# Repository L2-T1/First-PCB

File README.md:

# First-PCB
This my first PCB for learning and for the Solder activity ran by Hack Club

# Description
This project is creating a circuit board that powers 2 LED's that light up and have their brightness changed by a potentiometer.

# Bill of materials
- 2x LED's
- 2x Resisters
- 1x Single Battery-Cell
- 1x Rotary Potentiometer

# Screenshots

Made by Elliot on Slack 

Made as part of Hack Club Solder

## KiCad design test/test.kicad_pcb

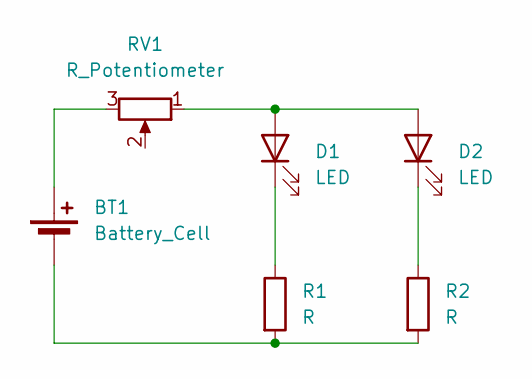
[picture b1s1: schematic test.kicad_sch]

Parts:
BT1: Battery_Cell; BatteryHolder_Keystone_3034_1x20mm
D1, D2: LED; LED_D5.0mm
R1, R2: R; R_Axial_DIN0207_L6.3mm_D2.5mm_P7.62mm_Horizontal
RV1: R_Potentiometer; Potentiometer_Vishay_T73YP_Vertical

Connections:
unnamed: BT1.1 (+), RV1.3
unnamed: BT1.2 (-), R1.2, R2.2
unnamed: D1.2 (A), D2.2 (A), RV1.1
unnamed: D1.1 (K), R1.1
unnamed: D2.1 (K), R2.1

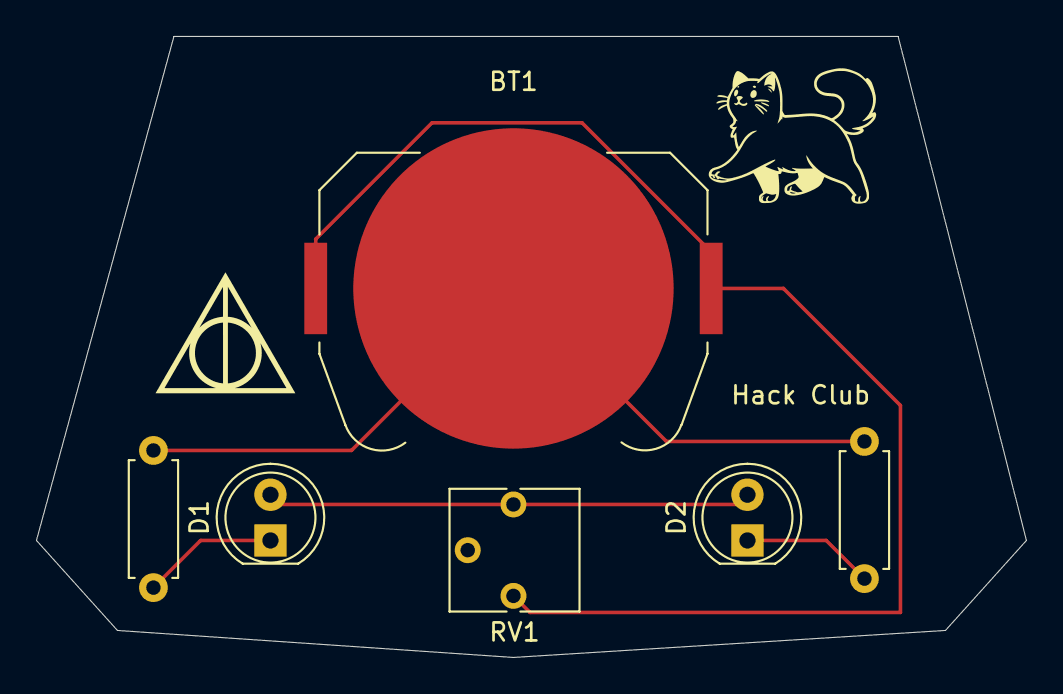
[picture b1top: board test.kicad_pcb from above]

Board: 2 copper layers, 55.0 x 34.5 mm, 6 parts (0 on the bottom side), 5 nets.
